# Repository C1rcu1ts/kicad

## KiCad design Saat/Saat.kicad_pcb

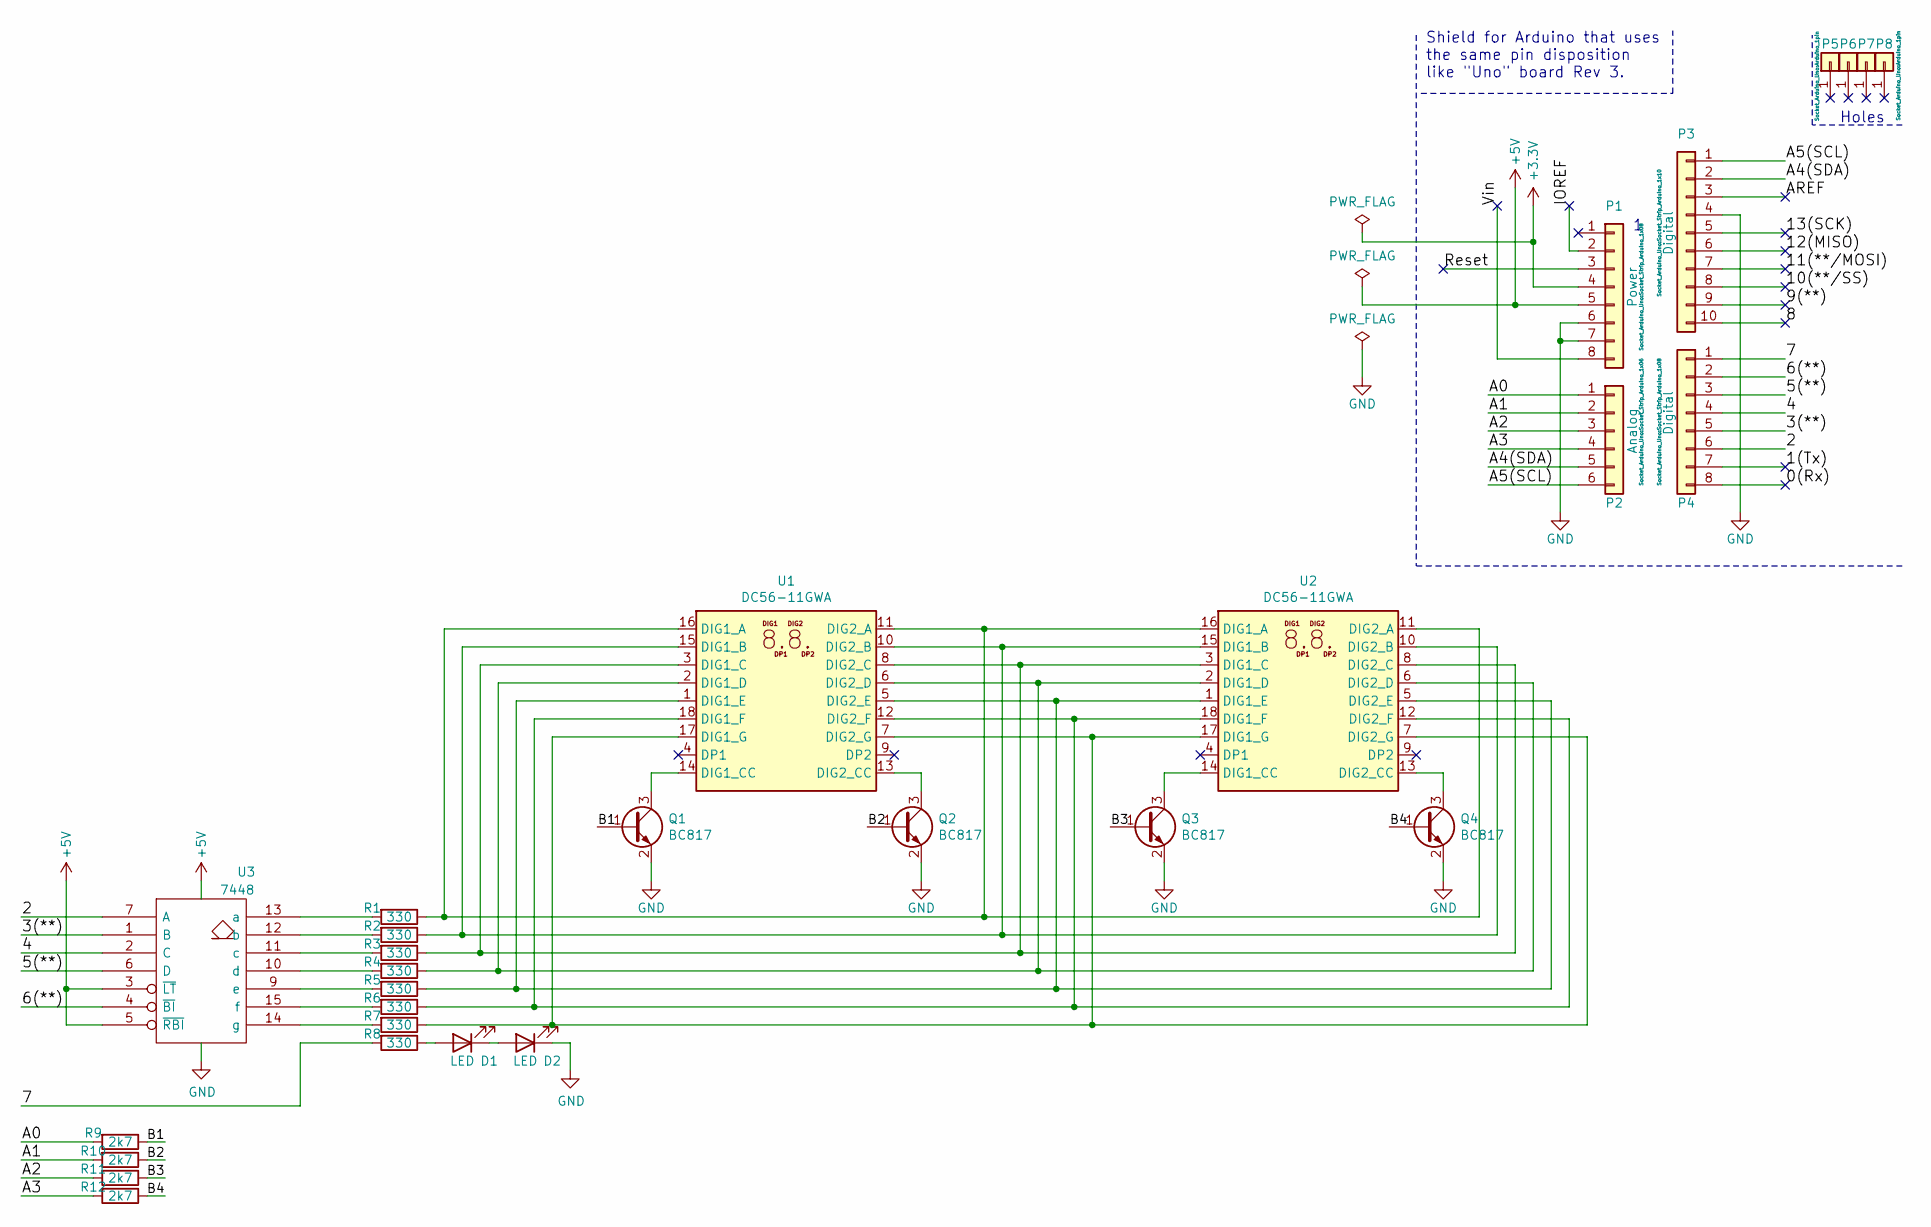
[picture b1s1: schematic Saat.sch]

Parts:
D1, D2: LED; LED_D3.0mm
P1: Power; Socket_Strip_Arduino_1x08
P2: Analog; Socket_Strip_Arduino_1x06
P3: Digital; Socket_Strip_Arduino_1x10
P4: Digital; Socket_Strip_Arduino_1x08
P5, P6, P7, P8: CONN_01X01; Arduino_1pin
Q1, Q2, Q3, Q4: BC817; SOT-23
R1, R2, R3, R4, R5, R6, R7, R8: 330; R_1206_3216Metric_Pad1.30x1.75mm_HandSolder
R9, R10, R11, R12: 2k7; R_1206_3216Metric_Pad1.30x1.75mm_HandSolder
U1, U2: DC56-11GWA; DA56-11CGKWA
U3: 7448; DIP-16_W7.62mm_LongPads

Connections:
+3V3: P1.4
+5V: P1.5, U3.3 (~LT), U3.5 (~RBI), U3.16 (VCC)
/0(Rx): P4.8
/1(Tx): P4.7
/2: P4.6, U3.7 (A)
/3(**): P4.5, U3.1 (B)
/4: P4.4, U3.2 (C)
/5(**): P4.3, U3.6 (D)
/6(**): P4.2, U3.4 (~BI)
/7: P4.1, R8.2
/8: P3.10
/9(**): P3.9
/10(**/SS): P3.8
/11(**/MOSI): P3.7
/12(MISO): P3.6
/13(SCK): P3.5
/A0: P2.1, R9.2
/A1: P2.2, R10.2
/A2: P2.3, R11.2
/A3: P2.4, R12.2
/A4(SDA): P2.5, P3.2
/A5(SCL): P2.6, P3.1
/AREF: P3.3
/B1: Q1.1 (B), R9.1
/B2: Q2.1 (B), R10.1
/B3: Q3.1 (B), R11.1
/B4: Q4.1 (B), R12.1
/IOREF: P1.2
/Reset: P1.3
/Vin: P1.8
GND: D2.1 (K), P1.6, P1.7, P3.4, Q1.2 (E), Q2.2 (E), Q3.2 (E), Q4.2 (E), U3.8 (GND)
unnamed: D1.1 (K), D2.2 (A)
unnamed: D1.2 (A), R8.1
unnamed: Q1.3 (C), U1.14 (DIG1_CC)
unnamed: Q2.3 (C), U1.13 (DIG2_CC)
unnamed: Q3.3 (C), U2.14 (DIG1_CC)
unnamed: Q4.3 (C), U2.13 (DIG2_CC)
unnamed: R1.1, U1.11 (DIG2_A), U1.16 (DIG1_A), U2.11 (DIG2_A), U2.16 (DIG1_A)
unnamed: R1.2, U3.13 (a)
unnamed: R2.1, U1.10 (DIG2_B), U1.15 (DIG1_B), U2.10 (DIG2_B), U2.15 (DIG1_B)
unnamed: R2.2, U3.12 (b)
unnamed: R3.1, U1.3 (DIG1_C), U1.8 (DIG2_C), U2.3 (DIG1_C), U2.8 (DIG2_C)
unnamed: R3.2, U3.11 (c)
unnamed: R4.1, U1.2 (DIG1_D), U1.6 (DIG2_D), U2.2 (DIG1_D), U2.6 (DIG2_D)
unnamed: R4.2, U3.10 (d)
unnamed: R5.1, U1.1 (DIG1_E), U1.5 (DIG2_E), U2.1 (DIG1_E), U2.5 (DIG2_E)
unnamed: R5.2, U3.9 (e)
unnamed: R6.1, U1.12 (DIG2_F), U1.18 (DIG1_F), U2.12 (DIG2_F), U2.18 (DIG1_F)
unnamed: R6.2, U3.15 (f)
unnamed: R7.1, U1.7 (DIG2_G), U1.17 (DIG1_G), U2.7 (DIG2_G), U2.17 (DIG1_G)
unnamed: R7.2, U3.14 (g)

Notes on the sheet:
Holes
Shield for Arduino that uses the same pin disposition like "Uno" board Rev 3.

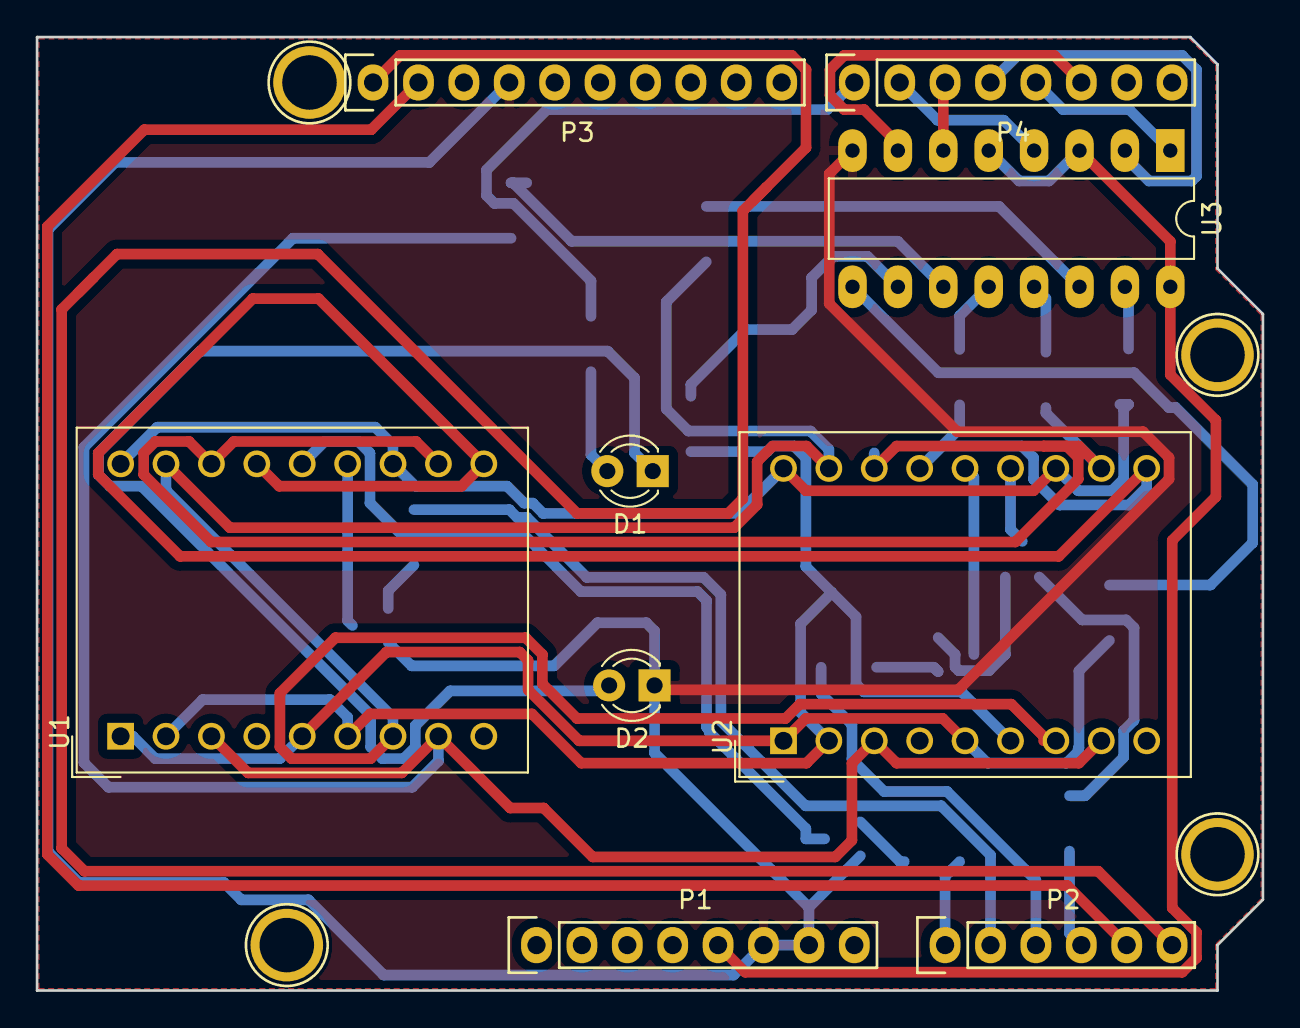
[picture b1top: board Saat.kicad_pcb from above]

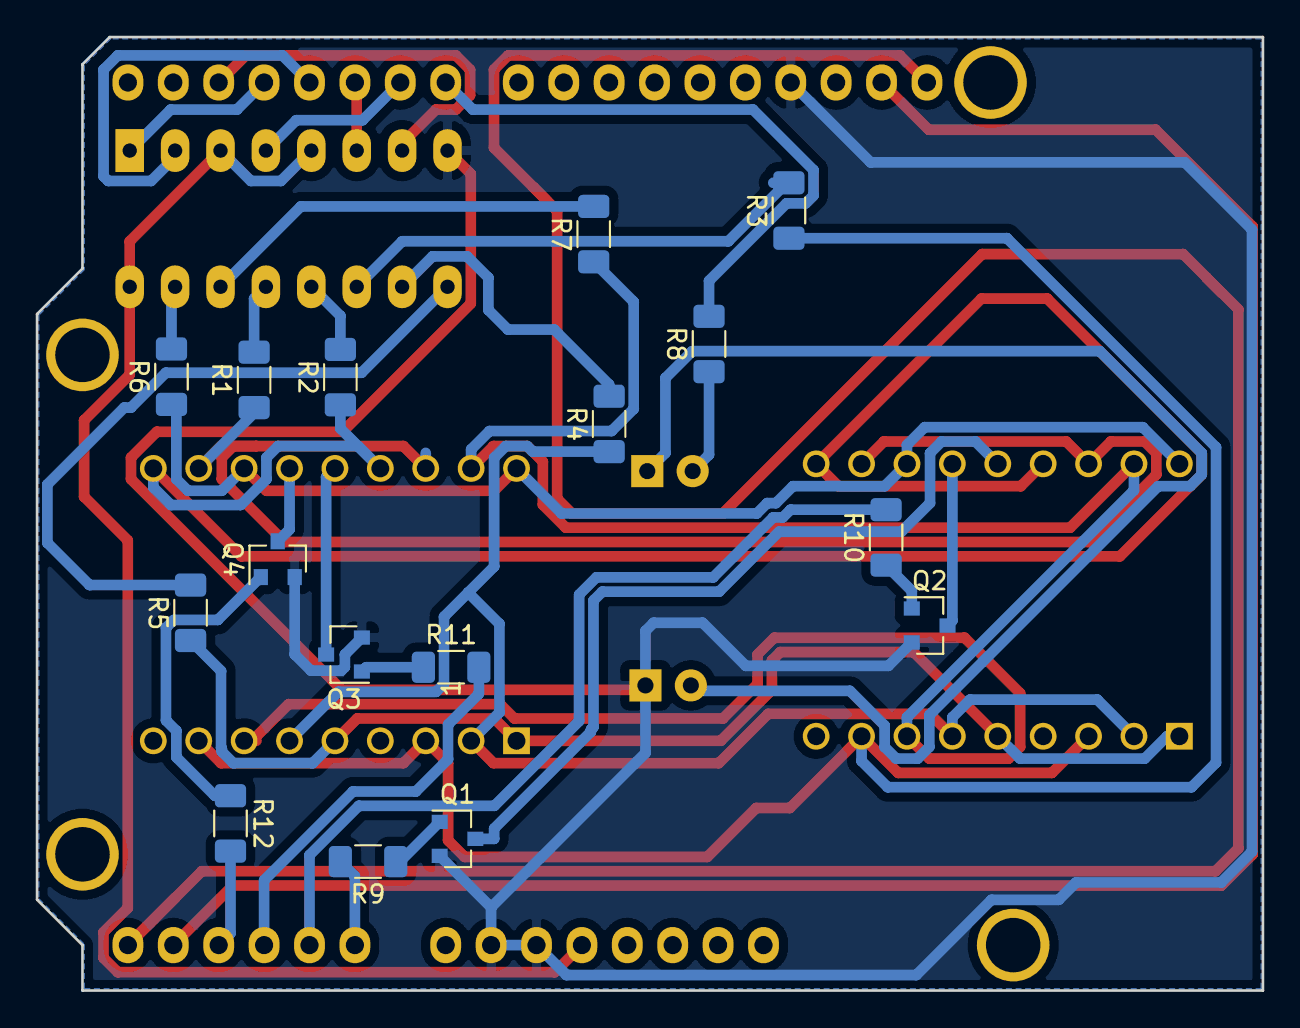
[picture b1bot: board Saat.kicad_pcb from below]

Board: 2 copper layers, 68.6 x 53.3 mm, 29 parts (16 on the bottom side), 38 nets.

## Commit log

2022-05-22 circuit
    design
